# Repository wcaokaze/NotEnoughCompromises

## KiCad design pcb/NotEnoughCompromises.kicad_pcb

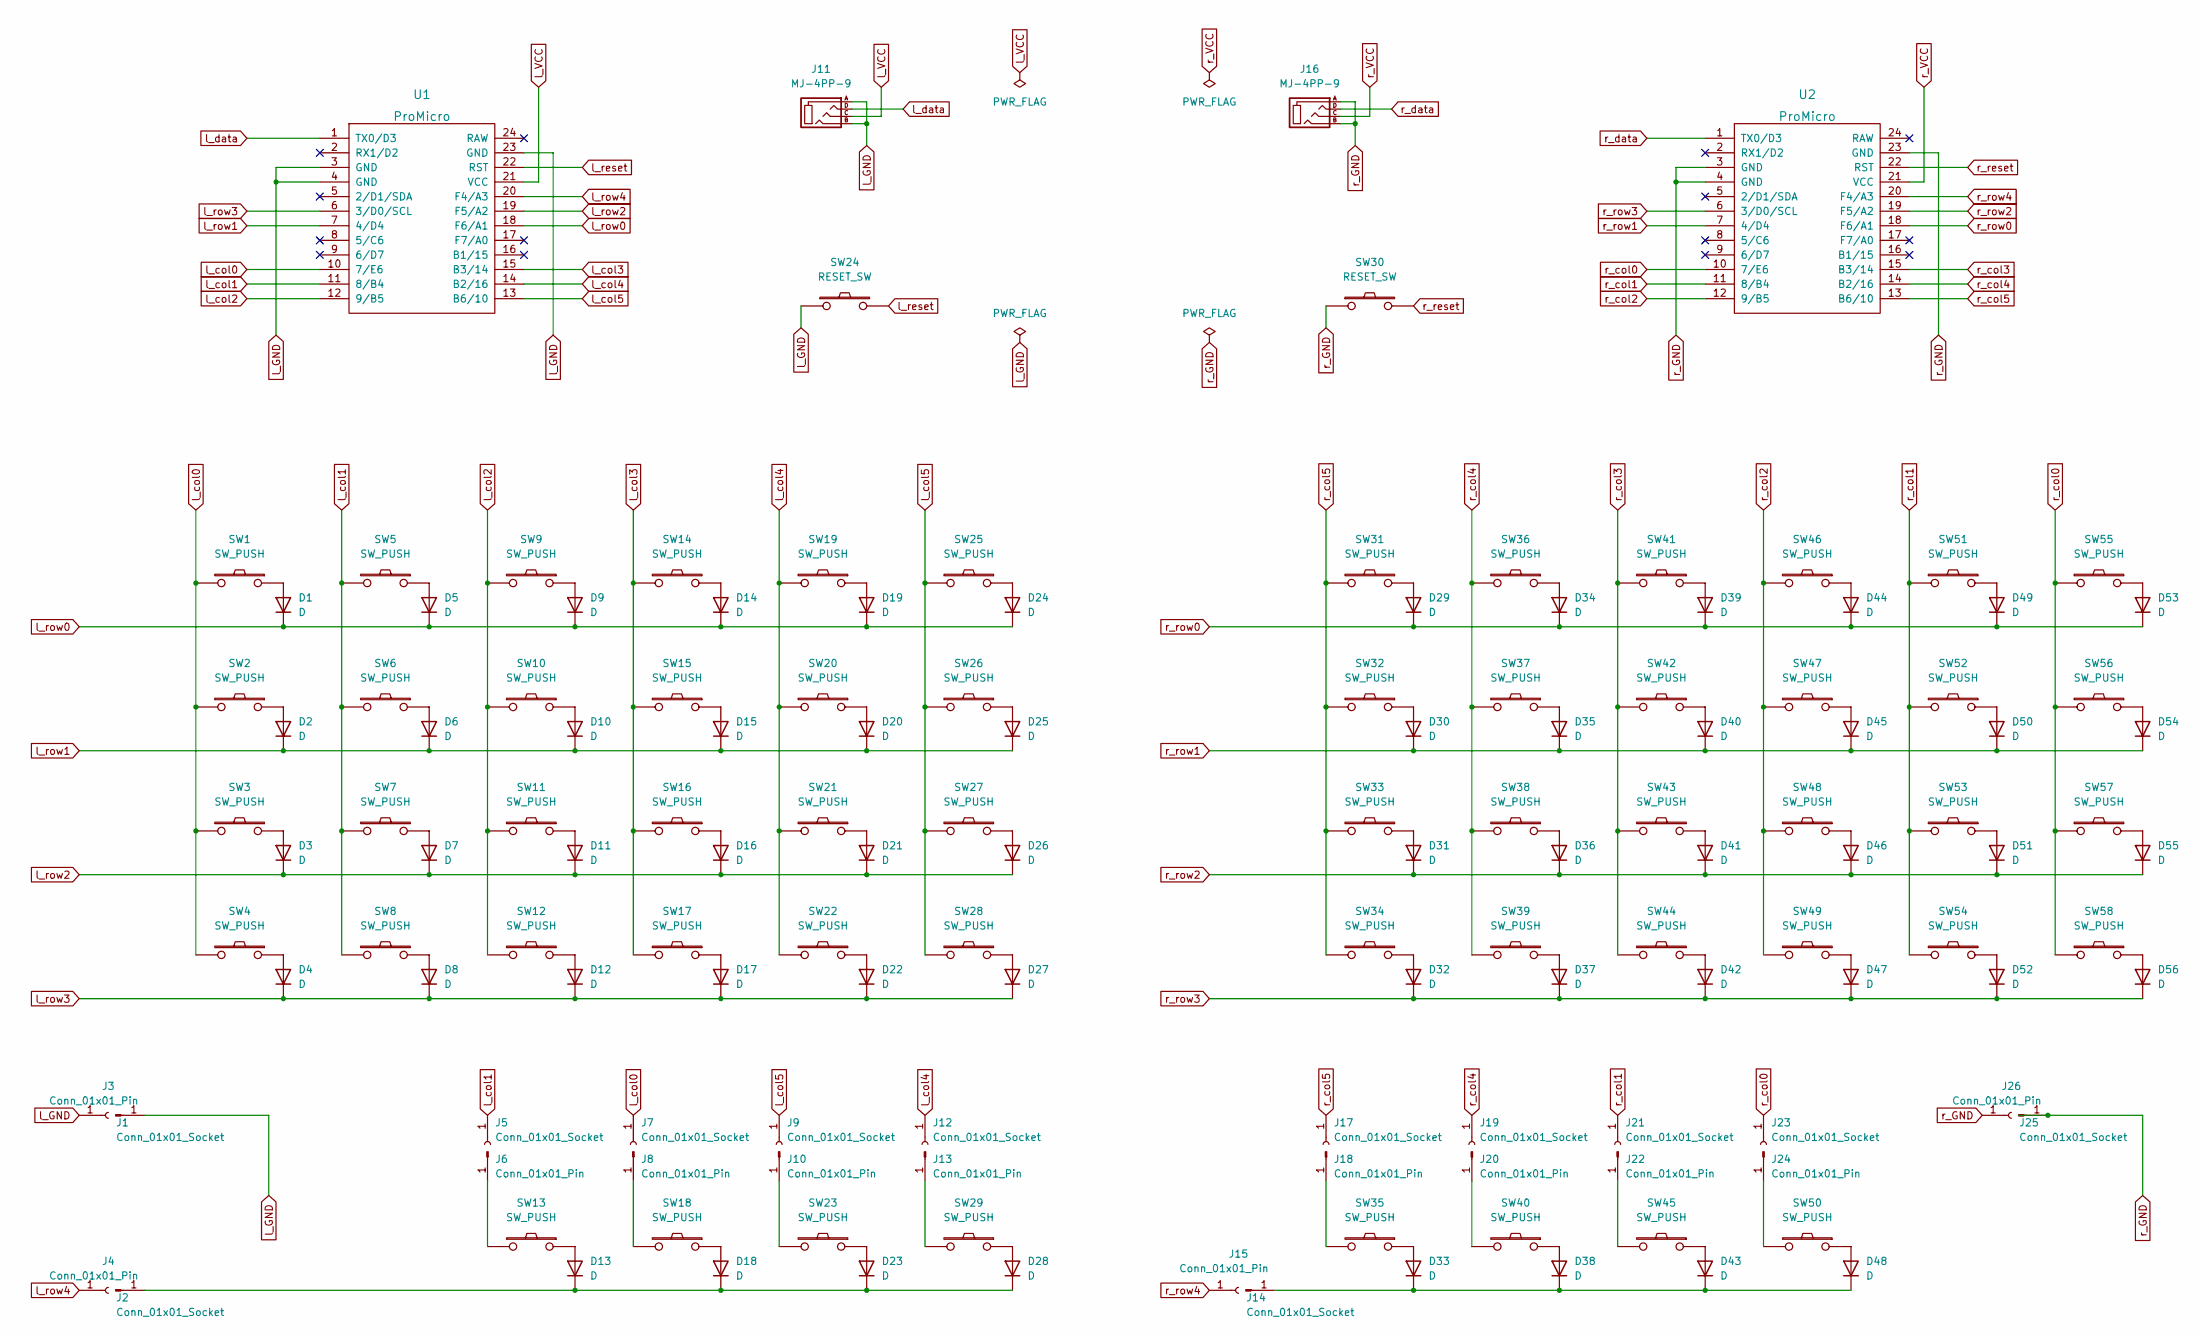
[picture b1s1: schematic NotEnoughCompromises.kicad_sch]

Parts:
D1, D2, D3, D4, D5, D6, D7, D8, D9, D10, D11, D12, D13, D14, D15, D16, D17, D18, D19, D20, D21, D22, D23, D24, D25, D26, D27, D28, D29, D30, D31, D32, D33, D34, D35, D36, D37, D38, D39, D40, D41, D42, D43, D44, D45, D46, D47, D48, D49, D50, D51, D52, D53, D54, D55, D56: D; D3_SMD_v2
J1, J2, J5, J7, J9, J12, J14, J17, J19, J21, J23, J25: Conn_01x01_Socket; SolderWirePad_1x01_SMD_1x2mm
J3, J4, J6, J8, J10, J13, J15, J18, J20, J22, J24, J26: Conn_01x01_Pin; SolderWirePad_1x01_SMD_1x2mm
J11, J16: MJ-4PP-9; MJ-4PP-9_1side
SW1, SW2, SW3, SW4, SW5, SW6, SW7, SW8, SW9, SW10, SW11, SW12, SW13, SW14, SW15, SW16, SW17, SW18, SW19, SW20, SW21, SW22, SW23, SW25, SW26, SW27, SW28, SW29, SW31, SW32, SW33, SW34, SW35, SW36, SW37, SW38, SW39, SW40, SW41, SW42, SW43, SW44, SW45, SW46, SW47, SW48, SW49, SW50, SW51, SW52, SW53, SW54, SW55, SW56, SW57, SW58: SW_PUSH; choc_v1
SW24, SW30: RESET_SW; reset_sw
U1, U2: ProMicro; ProMicro_v3.5

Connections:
unnamed: D1.2 (A), SW1.1
unnamed: D2.2 (A), SW2.1
unnamed: D3.2 (A), SW3.1
unnamed: D4.2 (A), SW4.1
unnamed: D5.2 (A), SW5.1
unnamed: D6.2 (A), SW6.1
unnamed: D7.2 (A), SW7.1
unnamed: D8.2 (A), SW8.1
unnamed: D9.2 (A), SW9.1
unnamed: D10.2 (A), SW10.1
unnamed: D11.2 (A), SW11.1
unnamed: D12.2 (A), SW12.1
unnamed: D13.2 (A), SW13.1
unnamed: D13.1 (K), D18.1 (K), D23.1 (K), D28.1 (K), J4.1
unnamed: D14.2 (A), SW14.1
unnamed: D15.2 (A), SW15.1
unnamed: D16.2 (A), SW16.1
unnamed: D17.2 (A), SW17.1
unnamed: D18.2 (A), SW18.1
unnamed: D19.2 (A), SW19.1
unnamed: D20.2 (A), SW20.1
unnamed: D21.2 (A), SW21.1
unnamed: D22.2 (A), SW22.1
unnamed: D23.2 (A), SW23.1
unnamed: D24.2 (A), SW25.1
unnamed: D25.2 (A), SW26.1
unnamed: D26.2 (A), SW27.1
unnamed: D27.2 (A), SW28.1
unnamed: D28.2 (A), SW29.1
unnamed: D29.2 (A), SW31.1
unnamed: D30.2 (A), SW32.1
unnamed: D31.2 (A), SW33.1
unnamed: D32.2 (A), SW34.1
unnamed: D33.2 (A), SW35.1
unnamed: D33.1 (K), D38.1 (K), D43.1 (K), D48.1 (K), J15.1
unnamed: D34.2 (A), SW36.1
unnamed: D35.2 (A), SW37.1
unnamed: D36.2 (A), SW38.1
unnamed: D37.2 (A), SW39.1
unnamed: D38.2 (A), SW40.1
unnamed: D39.2 (A), SW41.1
unnamed: D40.2 (A), SW42.1
unnamed: D41.2 (A), SW43.1
unnamed: D42.2 (A), SW44.1
unnamed: D43.2 (A), SW45.1
unnamed: D44.2 (A), SW46.1
unnamed: D45.2 (A), SW47.1
unnamed: D46.2 (A), SW48.1
unnamed: D47.2 (A), SW49.1
unnamed: D48.2 (A), SW50.1
unnamed: D49.2 (A), SW51.1
unnamed: D50.2 (A), SW52.1
unnamed: D51.2 (A), SW53.1
unnamed: D52.2 (A), SW54.1
unnamed: D53.2 (A), SW55.1
unnamed: D54.2 (A), SW56.1
unnamed: D55.2 (A), SW57.1
unnamed: D56.2 (A), SW58.1
unnamed: J6.1, SW13.2
unnamed: J8.1, SW18.2
unnamed: J10.1, SW23.2
unnamed: J13.1, SW29.2
unnamed: J18.1, SW35.2
unnamed: J20.1, SW40.2
unnamed: J22.1, SW45.2
unnamed: J24.1, SW50.2
l_GND: J1.1, J3.1, J11.A, J11.B, SW24.1, U1.3 (GND), U1.4 (GND), U1.23 (GND)
l_VCC: J11.C, U1.21 (VCC)
l_col0: J7.1, SW1.2, SW2.2, SW3.2, SW4.2, U1.10 (7/E6)
l_col1: J5.1, SW5.2, SW6.2, SW7.2, SW8.2, U1.11 (8/B4)
l_col2: SW9.2, SW10.2, SW11.2, SW12.2, U1.12 (9/B5)
l_col3: SW14.2, SW15.2, SW16.2, SW17.2, U1.15 (B3/14)
l_col4: J12.1, SW19.2, SW20.2, SW21.2, SW22.2, U1.14 (B2/16)
l_col5: J9.1, SW25.2, SW26.2, SW27.2, SW28.2, U1.13 (B6/10)
l_data: J11.D, U1.1 (TX0/D3)
l_reset: SW24.2, U1.22 (RST)
l_row0: D1.1 (K), D5.1 (K), D9.1 (K), D14.1 (K), D19.1 (K), D24.1 (K), U1.18 (F6/A1)
l_row1: D2.1 (K), D6.1 (K), D10.1 (K), D15.1 (K), D20.1 (K), D25.1 (K), U1.7 (4/D4)
l_row2: D3.1 (K), D7.1 (K), D11.1 (K), D16.1 (K), D21.1 (K), D26.1 (K), U1.19 (F5/A2)
l_row3: D4.1 (K), D8.1 (K), D12.1 (K), D17.1 (K), D22.1 (K), D27.1 (K), U1.6 (3/D0/SCL)
l_row4: J2.1, U1.20 (F4/A3)
r_GND: J16.A, J16.B, J25.1, J26.1, SW30.1, U2.3 (GND), U2.4 (GND), U2.23 (GND)
r_VCC: J16.C, U2.21 (VCC)
r_col0: J23.1, SW55.2, SW56.2, SW57.2, SW58.2, U2.10 (7/E6)
r_col1: J21.1, SW51.2, SW52.2, SW53.2, SW54.2, U2.11 (8/B4)
r_col2: SW46.2, SW47.2, SW48.2, SW49.2, U2.12 (9/B5)
r_col3: SW41.2, SW42.2, SW43.2, SW44.2, U2.15 (B3/14)
r_col4: J19.1, SW36.2, SW37.2, SW38.2, SW39.2, U2.14 (B2/16)
r_col5: J17.1, SW31.2, SW32.2, SW33.2, SW34.2, U2.13 (B6/10)
r_data: J16.D, U2.1 (TX0/D3)
r_reset: SW30.2, U2.22 (RST)
r_row0: D29.1 (K), D34.1 (K), D39.1 (K), D44.1 (K), D49.1 (K), D53.1 (K), U2.18 (F6/A1)
r_row1: D30.1 (K), D35.1 (K), D40.1 (K), D45.1 (K), D50.1 (K), D54.1 (K), U2.7 (4/D4)
r_row2: D31.1 (K), D36.1 (K), D41.1 (K), D46.1 (K), D51.1 (K), D55.1 (K), U2.19 (F5/A2)
r_row3: D32.1 (K), D37.1 (K), D42.1 (K), D47.1 (K), D52.1 (K), D56.1 (K), U2.6 (3/D0/SCL)
r_row4: J14.1, U2.20 (F4/A3)

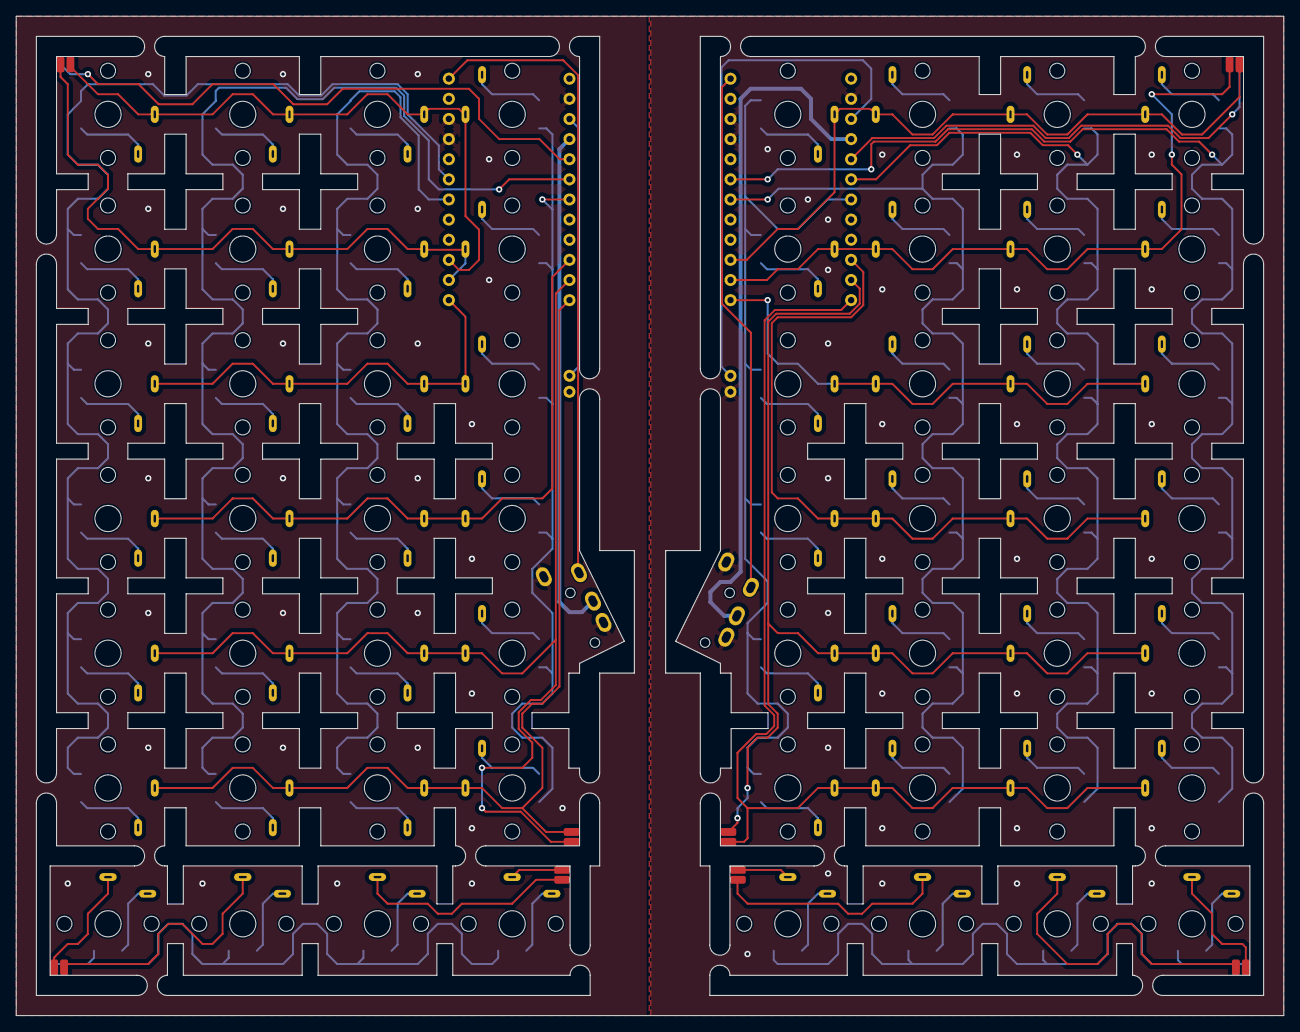
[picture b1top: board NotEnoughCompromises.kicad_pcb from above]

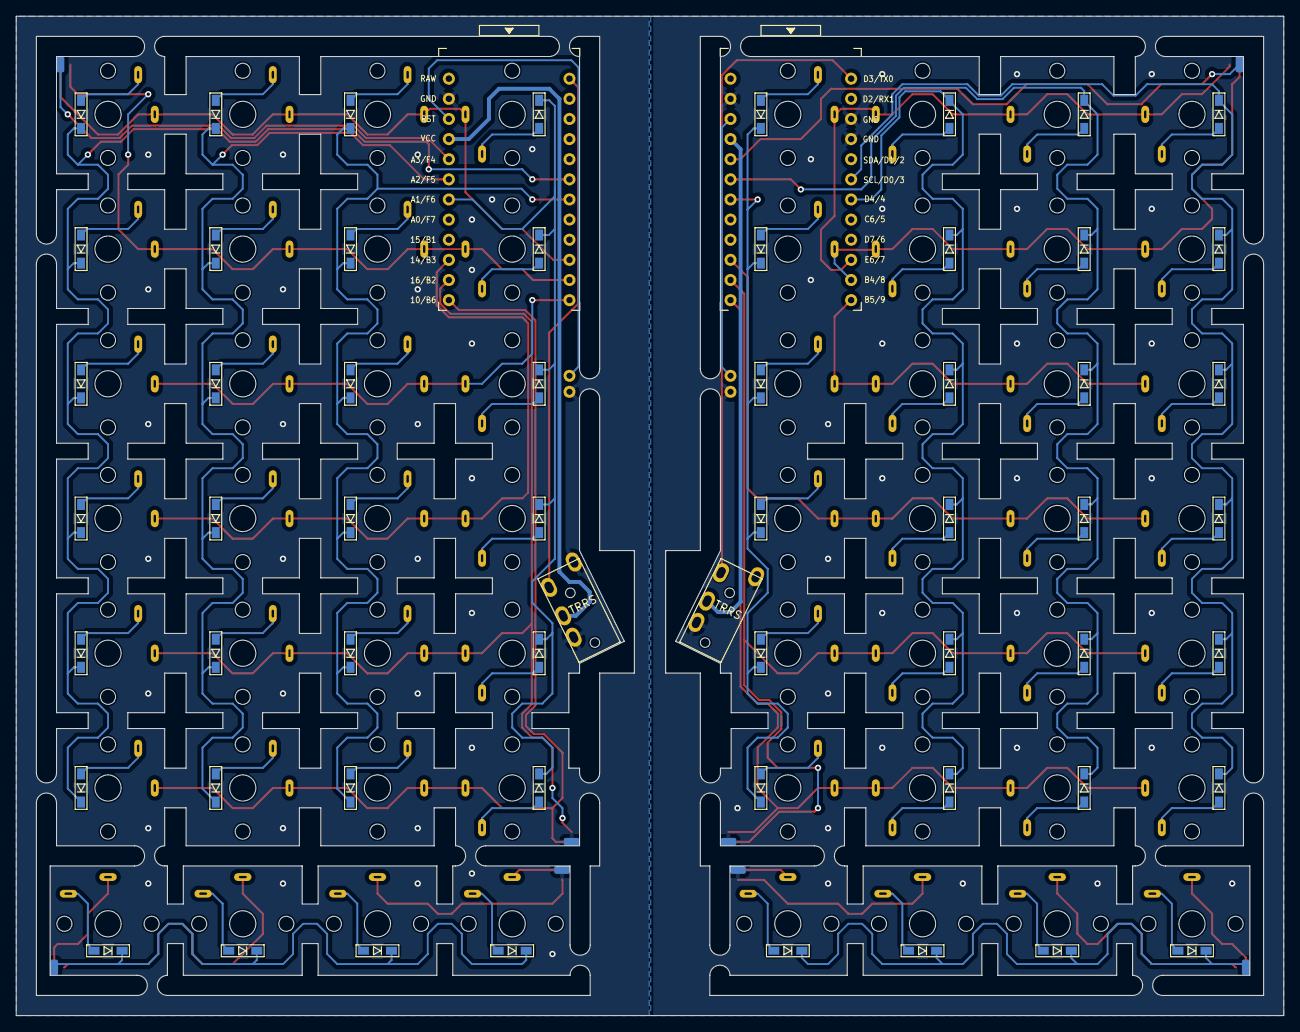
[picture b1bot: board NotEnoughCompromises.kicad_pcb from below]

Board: 2 copper layers, 159.9 x 126.1 mm, 142 parts (68 on the bottom side), 96 nets.

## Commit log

2023-09-12 親指部分のケースの大きさの立方体を置いた
2023-09-13 親指部分のケースにキースイッチを通すための穴を開けた
2023-09-14 thumb_caseの引数にprinter_friendly_position: boolを追加。trueのときプリンタにやさしい向きで出力するようにした
2023-09-14 基板の位置にcubeを置いた
2023-09-15 alphanumericのケースと基板を追加
2023-09-16 ゴム足の土台を作成
2023-09-17 ゴム足に開ける穴をケースの穴と同じにしてしまっていたのでスイッチの下半分の大きさに修正
2023-09-17 「左手前のキーの位置」にcase_placement_positionというややこしい名前がついていたのでcase_leftfront_key_placement_positionに変更
2023-09-17 なぜかハウジングという名称をすっかり忘れていたためハウジング関係の命名をhousingに変更
2023-09-18 キースイッチの各部位の位置がわかるようにした
2023-09-18 キーの位置計算をより正しく変更
2023-09-26 透明板の大きさのcubeを配置
2023-09-26 親指部のゴム足を追加
2023-09-27 透明板にケースとゴム足用のスペースを空けた
2023-09-30 基板の左右に余白を追加
2023-09-30 基板、一旦スイッチがあるとこだけにした
2023-09-30 基板のキースイッチ部分同士をつなげた
2023-10-01 透明板にキースイッチを通す穴を空けた
2023-10-02 透明板に基板配置ようのスペースを空けた
2023-10-04 透明板がケースの高さまで埋まるようにした
2023-10-07 親指キーの手前と数字行の奥にあった透明板の枠を外した
2023-10-09 include忘れなどを修正
2023-10-09 透明板の親指部分が0.1mm薄かったのを修正
2023-10-09 透明板を薄くした。基板に挿す部分だけ0.5mmはみ出させた
2023-10-10 ゴム足を基板の下に厚さ1mmで敷く形状に変更
2023-10-14 各パーツのmodule内でtranslateするようにした
2023-10-14 ゴム足にマイコン用のスペースを空けた
2023-10-14 チルトできるようにした
2023-10-14 ゴム足の四隅にマージンをつけた
2023-10-14 透明板を半透明にした
2023-10-20 透明板とゴム足の基板に挿す部分を作った
2023-10-20 ゴム足がキースイッチと干渉しないようにした
2023-10-27 ゴム足に透明板を挿す穴を開けた
2023-10-27 ゴム足、透明板もケースと同様にprinter_friendly_positionで出力できるようにした
2023-10-27 ゴム足に十分な厚さがあるときは透明板用の穴を貫通させないようにした
2023-10-29 added a submodule: foostan/kbd
2023-10-29 KiCadプロジェクト作成
2023-11-01 回路図を作成
2023-11-08 部品を配置した
2024-10-13 基板を作成
